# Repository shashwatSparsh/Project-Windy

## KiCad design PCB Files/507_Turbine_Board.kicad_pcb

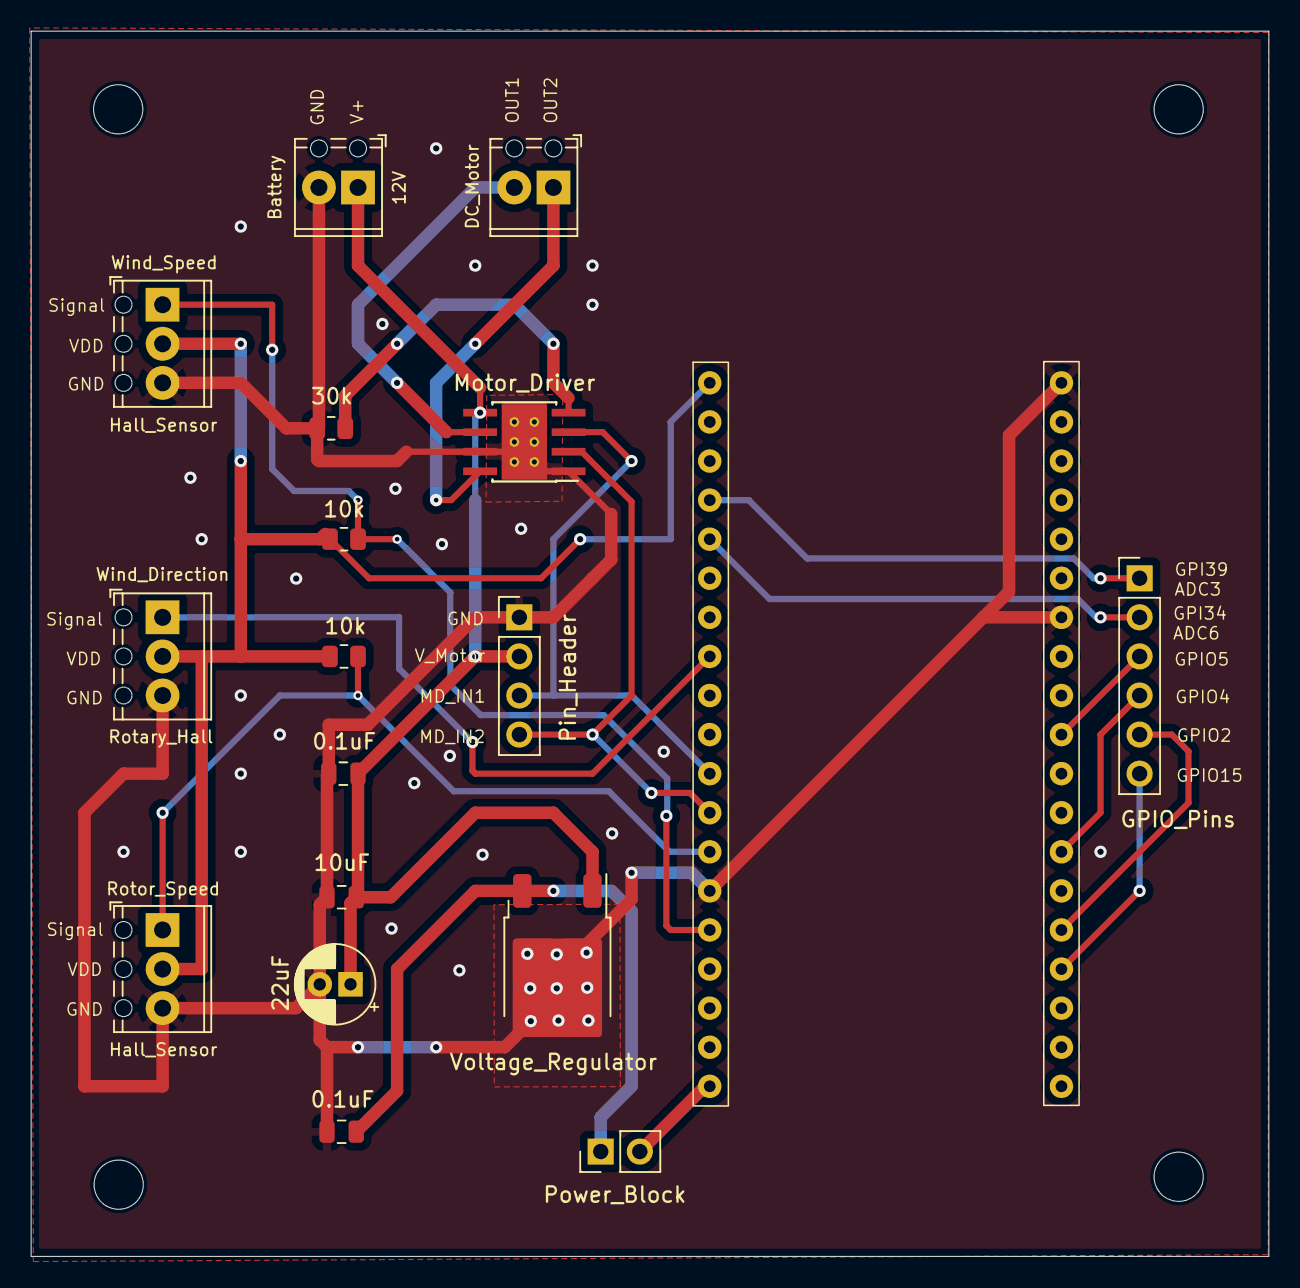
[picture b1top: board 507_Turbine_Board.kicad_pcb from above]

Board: 2 copper layers, 80.4 x 79.6 mm, 22 parts (0 on the bottom side), 19 nets.

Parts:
0.1uF, 0.1uF#2: 0.1uF; C_0805_2012Metric
10k, 10k#2: 10k; R_0805_2012Metric
10uF: 10uF; C_0805_2012Metric
12V: 12V; TerminalBlock_Phoenix_MPT-0,5-2-2.54_1x02_P2.54mm_Horizontal
30k: 30k; R_0805_2012Metric
DC_Motor: DC; TerminalBlock_Phoenix_MPT-0,5-2-2.54_1x02_P2.54mm_Horizontal
ESP1: ESP32_NodeMCU_KeeYees
H1, H2, H3, H4: MountingHole; MountingHole_3.2mm_M3
Motor_Driver: DRV8871; Texas_HTSOP-8-1EP_3.9x4.9mm_P1.27mm_EP2.95x4.9mm_Mask2.4x3.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
Pin_Header: 1x4 Motor_Driver; PinHeader_1x04_P2.54mm_Vertical
Pin_Header2: Power_Block; PinHeader_1x02_P2.54mm_Vertical
Pin_Header3: 1x6 GPIO; PinHeader_1x06_P2.54mm_Vertical
Polarized_Cap(22uF)1: 22uF; CP_Radial_D5.0mm_P2.00mm
Rotor_Speed: A1103ELHL; TerminalBlock_Phoenix_MPT-0,5-3-2.54_1x03_P2.54mm_Horizontal
Voltage_Regulator: KA78M05_TO252; TO-252-2
Wind_Direction: MA3A10250N; TerminalBlock_Phoenix_MPT-0,5-3-2.54_1x03_P2.54mm_Horizontal
Wind_Speed: A1103ELHL; TerminalBlock_Phoenix_MPT-0,5-3-2.54_1x03_P2.54mm_Horizontal

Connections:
/OUT1: DC_Motor.2, Motor_Driver.6 (OUT1)
/OUT2: DC_Motor.1, Motor_Driver.8 (OUT2)
ADC: ESP1.8 (GPIO33/ADC5), Wind_Direction.1
GND: 0.1uF.1, 0.1uF#2.1, 10uF.1, 12V.2, 30k.1, ESP1.14 (GND), ESP1.32 (GND), ESP1.38 (GND), Motor_Driver.1 (GND), Motor_Driver.7 (GND), Motor_Driver.9 (GND), Pin_Header.1, Polarized_Cap(22uF)1.2, Rotor_Speed.3, Voltage_Regulator.2 (GND), Wind_Direction.3, Wind_Speed.3
GPI15: ESP1.23 (GPIO15), Pin_Header3.6
GPI34/ADC6: ESP1.5 (GPI34/ADC6), Pin_Header3.2
GPI39/ADC3: ESP1.4 (GPI39/ADC3), Pin_Header3.1
GPIO2: ESP1.24 (GPIO2), Pin_Header3.5
GPIO4: ESP1.26 (GPIO4), Pin_Header3.4
GPIO5: ESP1.29 (GPIO5), Pin_Header3.3
GPIO12: 10k#2.2, ESP1.13 (GPIO12), Rotor_Speed.1
GPIO13: 10k.2, ESP1.15 (GPIO13), Wind_Speed.1
MD_IN1: ESP1.11 (GPIO27), Motor_Driver.3 (IN1), Pin_Header.3
MD_IN2: ESP1.12 (GPIO14), Motor_Driver.2 (IN2), Pin_Header.4
unnamed: 30k.2, Motor_Driver.4 (ILIM)
VDD: 10k.1, 10k#2.1, ESP1.1 (3V3), Rotor_Speed.2, Wind_Direction.2, Wind_Speed.2
V_Motor: 0.1uF.2, 10uF.2, 12V.1, Motor_Driver.5 (VM), Pin_Header.2, Polarized_Cap(22uF)1.1, Voltage_Regulator.1 (VI)
V_POWER: 0.1uF#2.2, Pin_Header2.1, Voltage_Regulator.3 (VO)
V_POWER2: ESP1.19 (Vin5V), Pin_Header2.2

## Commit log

2023-12-13 Adding Doxy Files and Work by Jacob Brooks
    Doxygen wizard files + log are added as a separate file.
    Jacob Brooks' work has been added as a separate folder with zipped files.
    His work has also been integrated into the main directory.
    PCB Files added as separate folder.
